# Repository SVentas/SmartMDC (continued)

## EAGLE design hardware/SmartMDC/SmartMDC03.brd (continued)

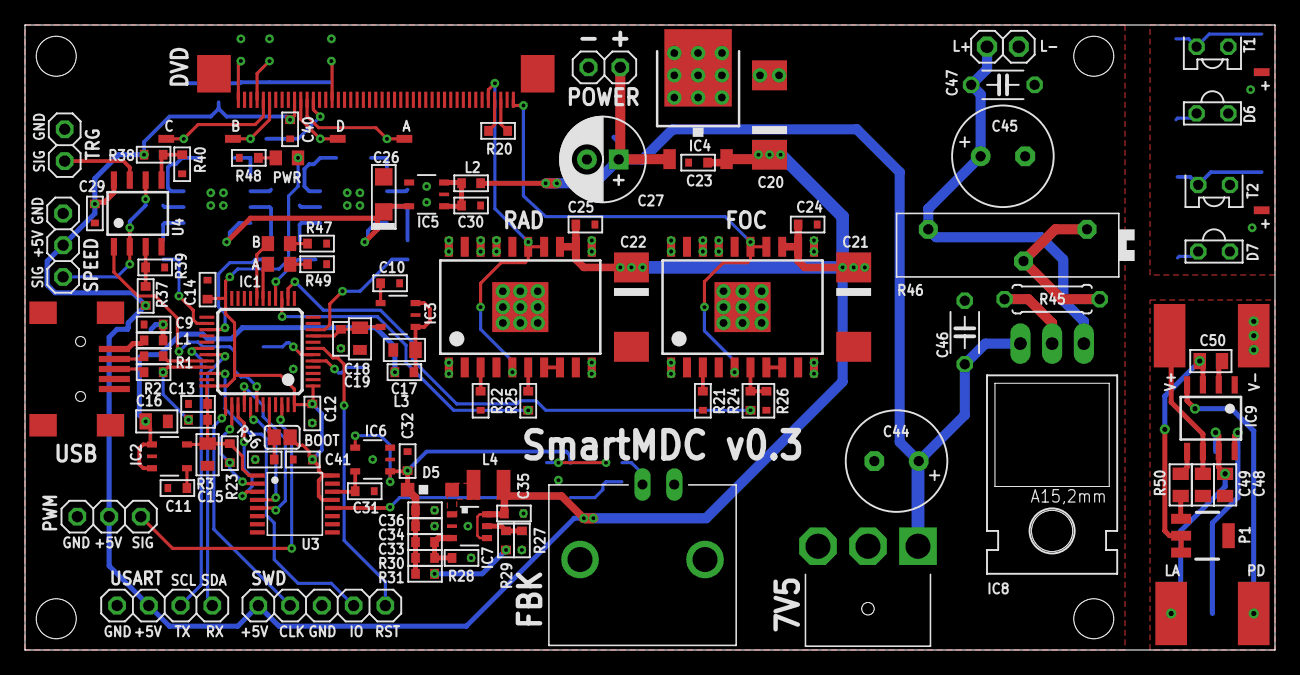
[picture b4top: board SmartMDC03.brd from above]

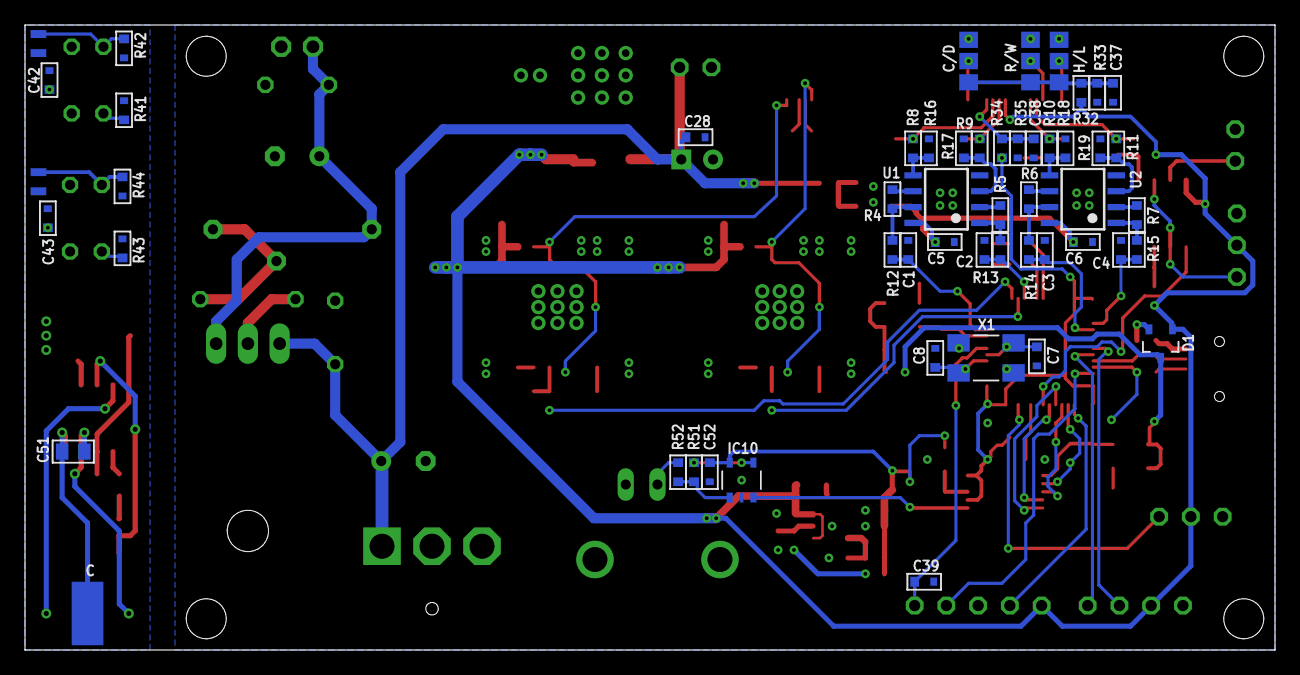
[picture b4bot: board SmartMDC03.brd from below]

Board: 2 copper layers, 100.0 x 50.0 mm, 166 parts (55 on the bottom side), 99 nets.

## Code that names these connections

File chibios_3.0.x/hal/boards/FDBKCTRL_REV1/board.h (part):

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#define GPIOB_SPI1_MISO         4U  // MISO
#define GPIOB_SPI1_MOSI         5U  // MOSI
#define GPIOB_TIM8_CH1          6U  // TRIGER IN
#define GPIOB_ALERT             7U  // NOT ALERT
#define GPIOB_PIN8              8U
#define GPIOB_PIN9              9U
#define GPIOB_PIN10             10U
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/*
 * GPIOA setup:
 *
 * PA0  - PIN0                      (input floating).
 * PA1  - PIN1                      (input floating).
 * PA2  - ADC1_CH3                  (analog floating).
 * PA3  - ADC1_CH4                  (analog floating).
 * PA4  - ADC2_CH1                  (analog floating).
 * PA5  - ADC2_CH2                  (analog floating).
 * PA6  - PIN6                      (input floating).
 * PA7  - PIN7                      (input floating).
 * PA8  - PIN8                      (input floating).
 * PA9  - I2C2_SCL                  (alternate 4).
 * PA10 - I2C2_SDA                  (alternate 4).
 * PA11 - USB_DM                    (alternate 14).
 * PA12 - USB_DP                    (alternate 14).
 * PA13 - SWDIO                     (alternate 0).
 * PA14 - SWCLK                     (alternate 0).
 * PA15 - SPI1_NSS                  (output pushpull).
 */
#define VAL_GPIOA_MODER             (PIN_MODE_INPUT(GPIOA_PIN0) |           \
                                     PIN_MODE_INPUT(GPIOA_PIN1) |           \
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/*
 * GPIOB setup:
 *
 * PB0  - LED_A                     (output pushpull).
 * PB1  - LED_B                     (output pushpull).
 * PB2  - PIN2                      (input floating).
 * PB3  - SPI1_SCK                  (alternate 5).
 * PB4  - SPI1_MISO                 (alternate 5).
 * PB5  - SPI1_MOSI                 (alternate 5).
 * PB6  - TIM8_CH1                  (alternate 5).
 * PB7  - ALERT                     (input floating).
 * PB8  - PIN8                      (input floating).
 * PB9  - PIN9                      (input floating).
 * PB10 - PIN10                     (input floating).
 * PB11 - PIN11                     (input floating).
 * PB12 - PIN12                     (input floating).
 * PB13 - ADC3_CH5                  (analog floating).
 * PB14 - ADC4_CH4                  (analog floating).
 * PB15 - PIN15                     (input floating).
 */
#define VAL_GPIOB_MODER             (PIN_MODE_OUTPUT(GPIOB_LED_A) |         \
                                     PIN_MODE_OUTPUT(GPIOB_LED_B) |         \
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 * PC12 - PIN12                     (input floating).
 * PC13 - PIN13                     (input floating).
 * PC14 - PIN14                     (input floating).
 * PC15 - PIN15                     (input floating).
 */
#define VAL_GPIOC_MODER             (PIN_MODE_INPUT(GPIOC_PIN0) |           \
                                     PIN_MODE_INPUT(GPIOC_PIN1) |           \
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/*
 * GPIOD setup:
 *
 * PD0  - PIN0                      (input floating).
 * PD1  - PIN1                      (input floating).
 * PD2  - PIN2                      (input floating).
 * PD3  - PIN3                      (input floating).
 * PD4  - PIN4                      (input floating).
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/*
 * GPIOF setup:
 *
 * PF0  - OSC_IN                    (input floating).
 * PF1  - OSC_OUT                   (input floating).
 * PF2  - PIN2                      (input floating).
 * PF3  - PIN3                      (input floating).
 * PF4  - PIN4                      (input floating).
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
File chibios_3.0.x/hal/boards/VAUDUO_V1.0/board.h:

/*
    ChibiOS - Copyright (C) 2006..2015 Giovanni Di Sirio

    Licensed under the Apache License, Version 2.0 (the "License");
    you may not use this file except in compliance with the License.
    You may obtain a copy of the License at

        http://www.apache.org/licenses/LICENSE-2.0

    Unless required by applicable law or agreed to in writing, software
    distributed under the License is distributed on an "AS IS" BASIS,
    WITHOUT WARRANTIES OR CONDITIONS OF ANY KIND, either express or implied.
    See the License for the specific language governing permissions and
    limitations under the License.
*/

#ifndef _BOARD_H_
#define _BOARD_H_

/*
 * Setup for the VauDUO v1.0 board.
 */

/*
 * Board identifier.
 */
#define BOARD_VAUDUO_V1_0
#define BOARD_NAME              "VauDUO v1.0"

/*
 * Board frequencies.
 */
#if !defined(STM32_LSECLK)
#define STM32_LSECLK            0
#endif

#if !defined(STM32_HSECLK)
#define STM32_HSECLK            8000000
#endif

/*
 * MCU type, supported types are defined in ./os/hal/platforms/hal_lld.h.
 */
#define STM32F10X_MD

/*
 * IO pins assignments.
 */
#define GPIOA_USB_DP            12
#define GPIOB_LED_A             3
#define GPIOB_LED_B             4
#define GPIOB_DRV_EN            5
#define GPIOB_SPI2NSS           12

/*
 * I/O ports initial setup, this configuration is established soon after reset
 * in the initialization code.
 *
 * The digits have the following meaning:
 *   0 - Analog input.
 *   1 - Push Pull output 10MHz.
 *   2 - Push Pull output 2MHz.
 *   3 - Push Pull output 50MHz.
 *   4 - Digital input.
 *   5 - Open Drain output 10MHz.
 *   6 - Open Drain output 2MHz.
 *   7 - Open Drain output 50MHz.
 *   8 - Digital input with PullUp or PullDown resistor depending on ODR.
 *   9 - Alternate Push Pull output 10MHz.
 *   A - Alternate Push Pull output 2MHz.
 *   B - Alternate Push Pull output 50MHz.
 *   C - Reserved.
 *   D - Alternate Open Drain output 10MHz.
 *   E - Alternate Open Drain output 2MHz.
 *   F - Alternate Open Drain output 50MHz.
 * Please refer to the STM32 Reference Manual for details.
 */

/*
 * Port A setup.
 * Everything floating input except:
 * PA0  - Alternate Push Pull output  (TIM2 CH1).
 * PA1  - Alternate Push Pull output  (TIM2 CH2).
 * PA2  - Alternate Push Pull output  (TIM2 CH3).
 * PA3  - Alternate Push Pull output  (TIM2 CH4).
 * PA4  - Not Used.
 * PA5  - Normal input                (INT).
 * PA6  - Normal input                (TIM3 CH1 - IN4).
 * PA7  - Normal input                (TIM3 CH2 - IN3).
 * PA8  - Not Used.
 * PA9  - Alternate Push Pull output  (USART1 TX).
 * PA10 - Normal Input                (USART1 RX).
 * PA11 - Normal input                (USB DM).
 * PA12 - Normal input                (USB DP).
 * PA13 - Pull-up input               (SWDIO).
 * PA14 - Pull-down input             (SWCLK).
 * PA15 - Not Used.
 */
#define VAL_GPIOACRL            0x4444AAAA      /*  PA7...PA0 */
#define VAL_GPIOACRH            0x488444A4      /* PA15...PA8 */
#define VAL_GPIOAODR            0x00002000

/*
 * Port B setup.
 * Everything floating input except:
 * PB0  - Normal input                (TIM3 CH3 - IN2).
 * PB1  - Normal input                (TIM3 CH4 - IN1).
 * PB2  - Normal input                (BOOT1).
 * PB3  - Push Pull output            (LEDA).
 * PB4  - Push Pull output            (LEDB).
 * PB5  - Push Pull output            (DRV_EN).
 * PB6  - Alternate Push Pull output  (TIM4_CH1).
 * PB7  - Alternate Push Pull output  (TIM4 CH2).
 * PB8  - Alternate Push Pull output  (TIM4 CH3).
 * PB9  - Alternate Push Pull output  (TIM4 CH4).
 * PB10 - Alternate Open Drain output (SCL).
 * PB11 - Alternate Open Drain output (SDA).
 * PB12 - Push Pull output            (SPI2 NSS).
 * PB13 - Alternate Push Pull output  (SPI2 SCK).
 * PB14 - Normal input                (SPI2 MISO).
 * PB15 - Alternate Push Pull output  (SPI2 MOSI).
 */
#define VAL_GPIOBCRL            0xBB222444      /*  PB7...PB0 */
#define VAL_GPIOBCRH            0xB4B2EEBB      /* PB15...PB8 */
#define VAL_GPIOBODR            0x00001018

/*
 * Port C setup.
 * Everything floating input except:
 * PC15 - Normal input (USBEN).
 */
#define VAL_GPIOCCRL            0x44444444      /*  PC7...PC0 */
#define VAL_GPIOCCRH            0x44444444      /* PC15...PC8 */
#define VAL_GPIOCODR            0x00000000

/*
 * Port D setup.
 * Everything floating input except:
 * PD0  - Normal input (XTAL).
 * PD1  - Normal input (XTAL).
 */
#define VAL_GPIODCRL            0x44444444      /*  PD7...PD0 */
#define VAL_GPIODCRH            0x44444444      /* PD15...PD8 */
#define VAL_GPIODODR            0x00000000

/*
 * Port E setup.
 * Everything floating input except:
 */
#define VAL_GPIOECRL            0x44444444      /*  PE7...PE0 */
#define VAL_GPIOECRH            0x44444444      /* PE15...PE8 */
#define VAL_GPIOEODR            0x00000000

/*
 * USB bus activation macro, required by the USB driver.
 */
#define usb_lld_connect_bus(usbp) { \
  palSetPadMode(GPIOA, GPIOA_USB_DP, PAL_MODE_INPUT); \
}

/*
 * USB bus de-activation macro, required by the USB driver.
 */
#define usb_lld_disconnect_bus(usbp) { \
  palSetPadMode(GPIOA, GPIOA_USB_DP, PAL_MODE_OUTPUT_PUSHPULL); \
  palClearPad(GPIOA, GPIOA_USB_DP); \
}

#if !defined(_FROM_ASM_)
#ifdef __cplusplus
extern "C" {
#endif
  void boardInit(void);
#ifdef __cplusplus
}
#endif
#endif /* _FROM_ASM_ */

#endif /* _BOARD_H_ */

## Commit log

2016-01-19 :tada: Added .gitattributes & .gitignore files
2016-01-19 The first content added.
2017-06-07 New hardware added
2017-10-08 Feedback Ctrl REV1 added
2017-10-10 PID rewrite & optimization
2017-10-10 Telemetry enhanced.
2017-10-11 AD5761R driver modified
2017-10-17 Minor update
2017-10-23 Optimization
